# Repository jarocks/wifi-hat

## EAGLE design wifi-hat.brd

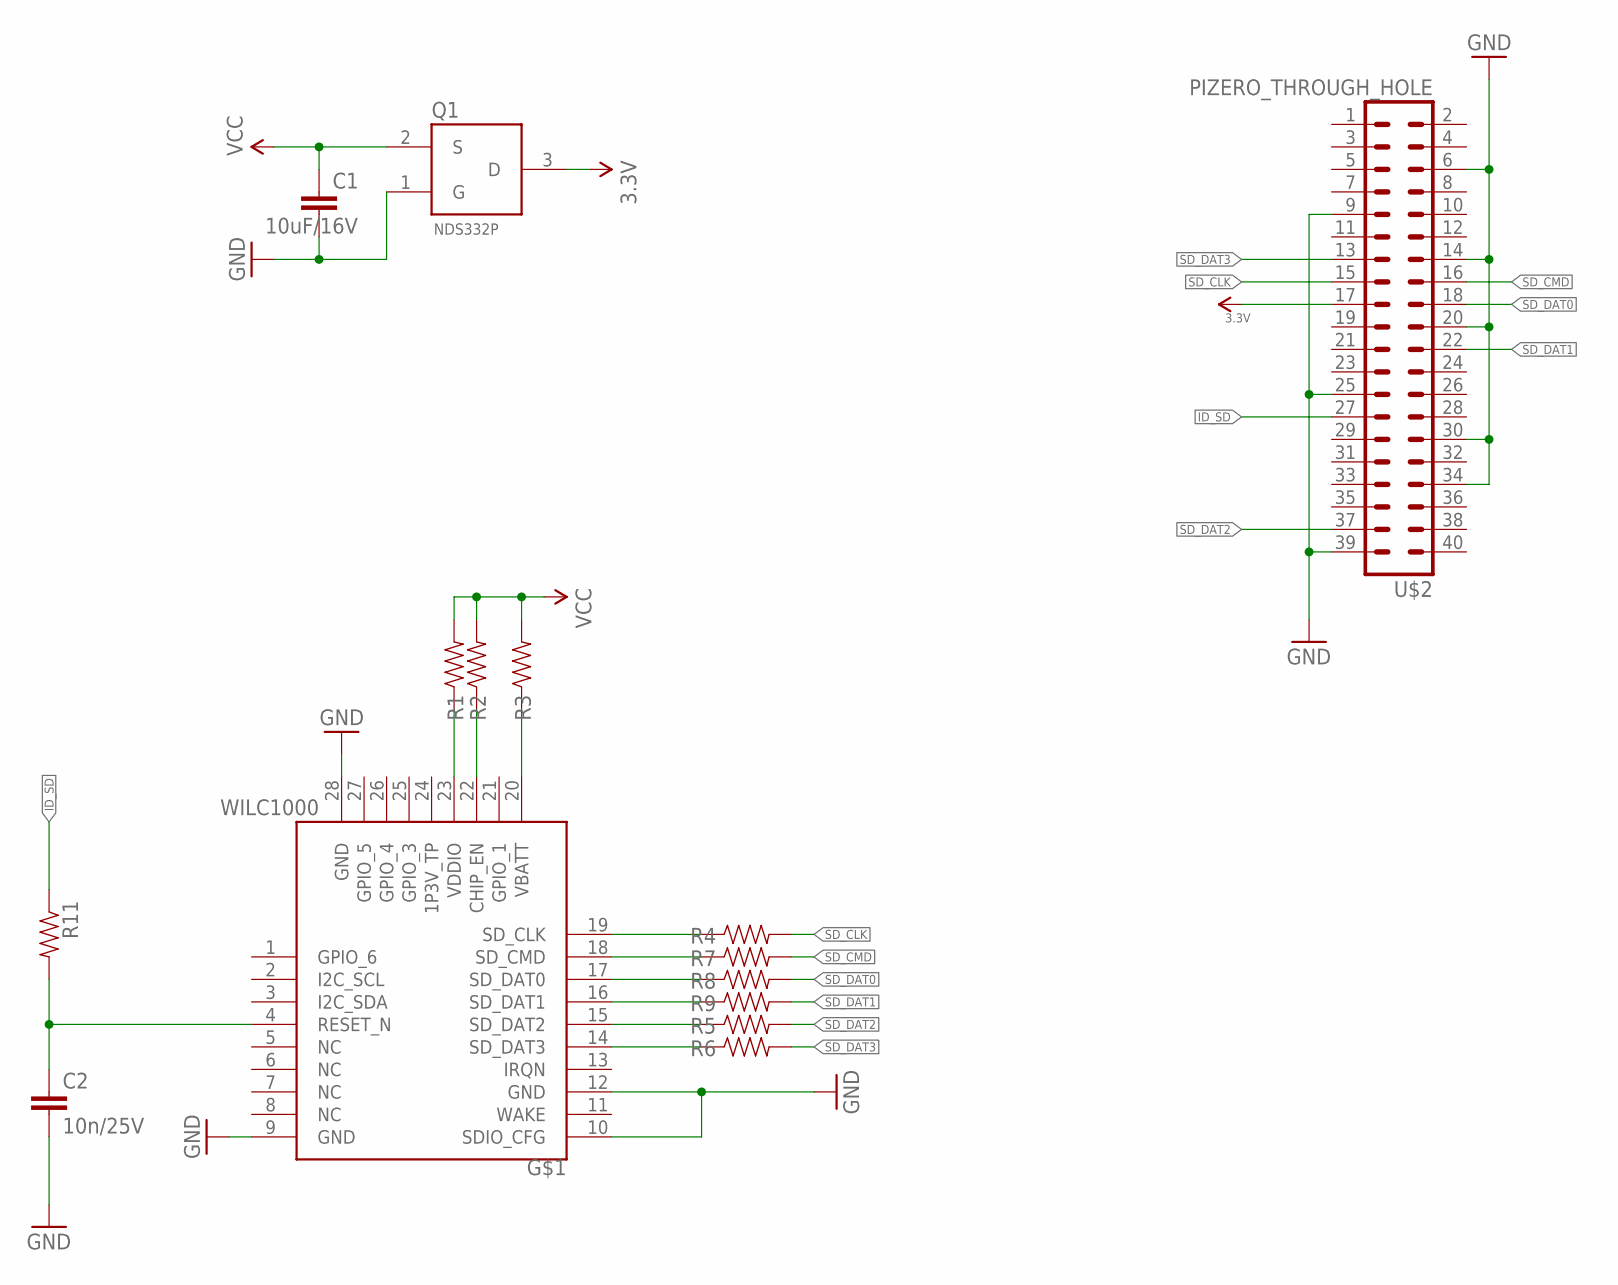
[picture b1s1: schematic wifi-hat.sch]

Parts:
C1: 10uF/16V; C0603K
C2: 10n/25V; C0603K
Q1: NDS332P; SOT23
R1, R3: 0 Ohm; 0603-RES
R2, R11: 1M Ohm; 0603-RES
R4, R5, R6, R7, R8, R9: 75 Ohm; 0603-RES
U$2: PIZERO_THROUGH_HOLE; PIZERO_THOUGH_HOLE
WI_SOC: WILC1000; ATWILC1000-MR110PA

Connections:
1P3V_TP: WI_SOC.24 (1P3V_TP)
3.3V: Q1.3 (D), U$2.17
GND: C1.2, C2.2, Q1.1 (G), U$2.6, U$2.9, U$2.14, U$2.20, U$2.25, U$2.30, U$2.34, U$2.39, WI_SOC.9 (GND), WI_SOC.10 (SDIO_CFG), WI_SOC.12 (GND), WI_SOC.28 (GND)
ID_SD: R11.1, U$2.27
unnamed: R2.1, WI_SOC.22 (CHIP_EN)
unnamed: R1.1, WI_SOC.23 (VDDIO)
unnamed: R3.1, WI_SOC.20 (VBATT)
unnamed: R7.1, WI_SOC.18 (SD_CMD)
unnamed: R8.1, WI_SOC.17 (SD_DAT0)
unnamed: R9.1, WI_SOC.16 (SD_DAT1)
unnamed: R5.1, WI_SOC.15 (SD_DAT2)
unnamed: R6.1, WI_SOC.14 (SD_DAT3)
unnamed: R4.1, WI_SOC.19 (SD_CLK)
RESET_N: C2.1, R11.2, WI_SOC.4 (RESET_N)
SD_CLK: R4.2, U$2.15
SD_CMD: R7.2, U$2.16
SD_DAT0: R8.2, U$2.18
SD_DAT1: R9.2, U$2.22
SD_DAT2: R5.2, U$2.37
SD_DAT3: R6.2, U$2.13
VCC: C1.1, Q1.2 (S), R1.2, R2.2, R3.2

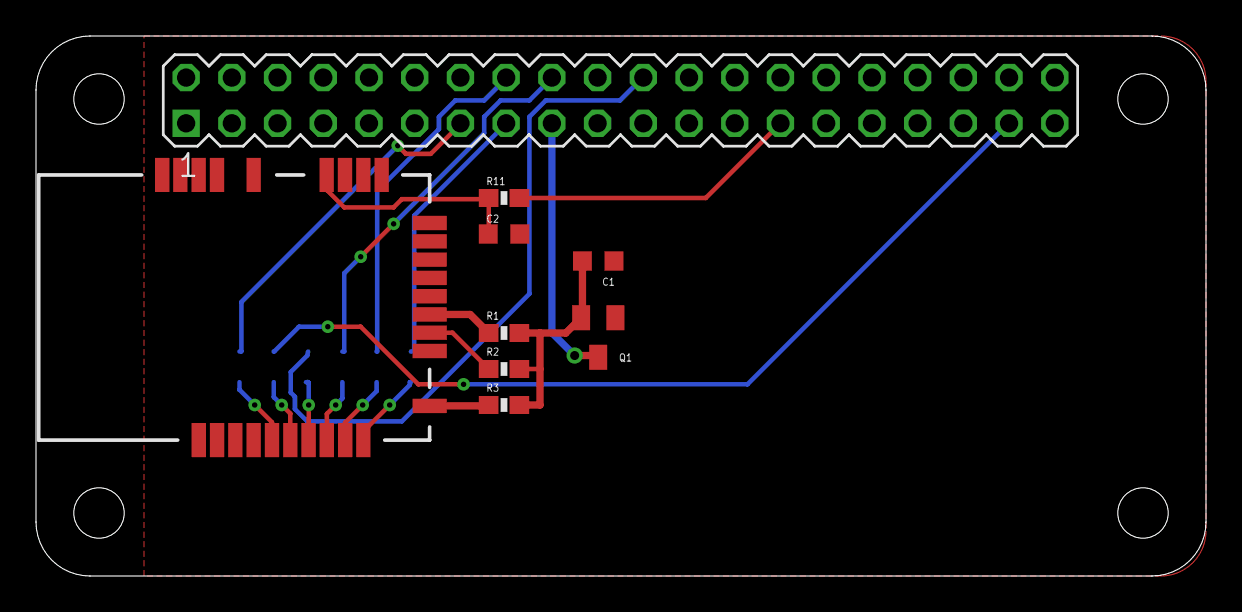
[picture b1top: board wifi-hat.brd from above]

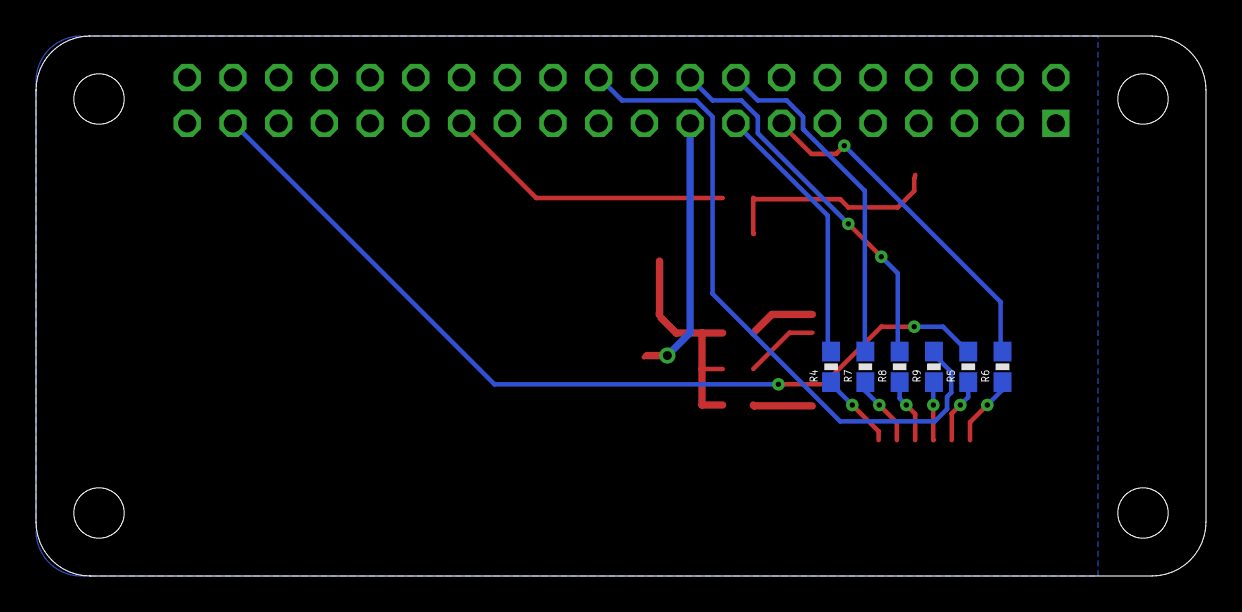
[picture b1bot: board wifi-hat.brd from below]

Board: 2 copper layers, 65.0 x 30.0 mm, 15 parts (6 on the bottom side), 20 nets.

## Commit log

2016-02-28 cleanup and fixes
    Cleaned up the board and schematic layouts. Connected RESET_N to GPIO to handle power cycling.
2016-03-08 Replace Caps with 603 variants

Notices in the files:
parts and their libraries:
SparkFun-Resistors: Licensing: Creative Commons ShareAlike 4.0 International - https://creativecommons.org/licenses/by-sa/4.0
